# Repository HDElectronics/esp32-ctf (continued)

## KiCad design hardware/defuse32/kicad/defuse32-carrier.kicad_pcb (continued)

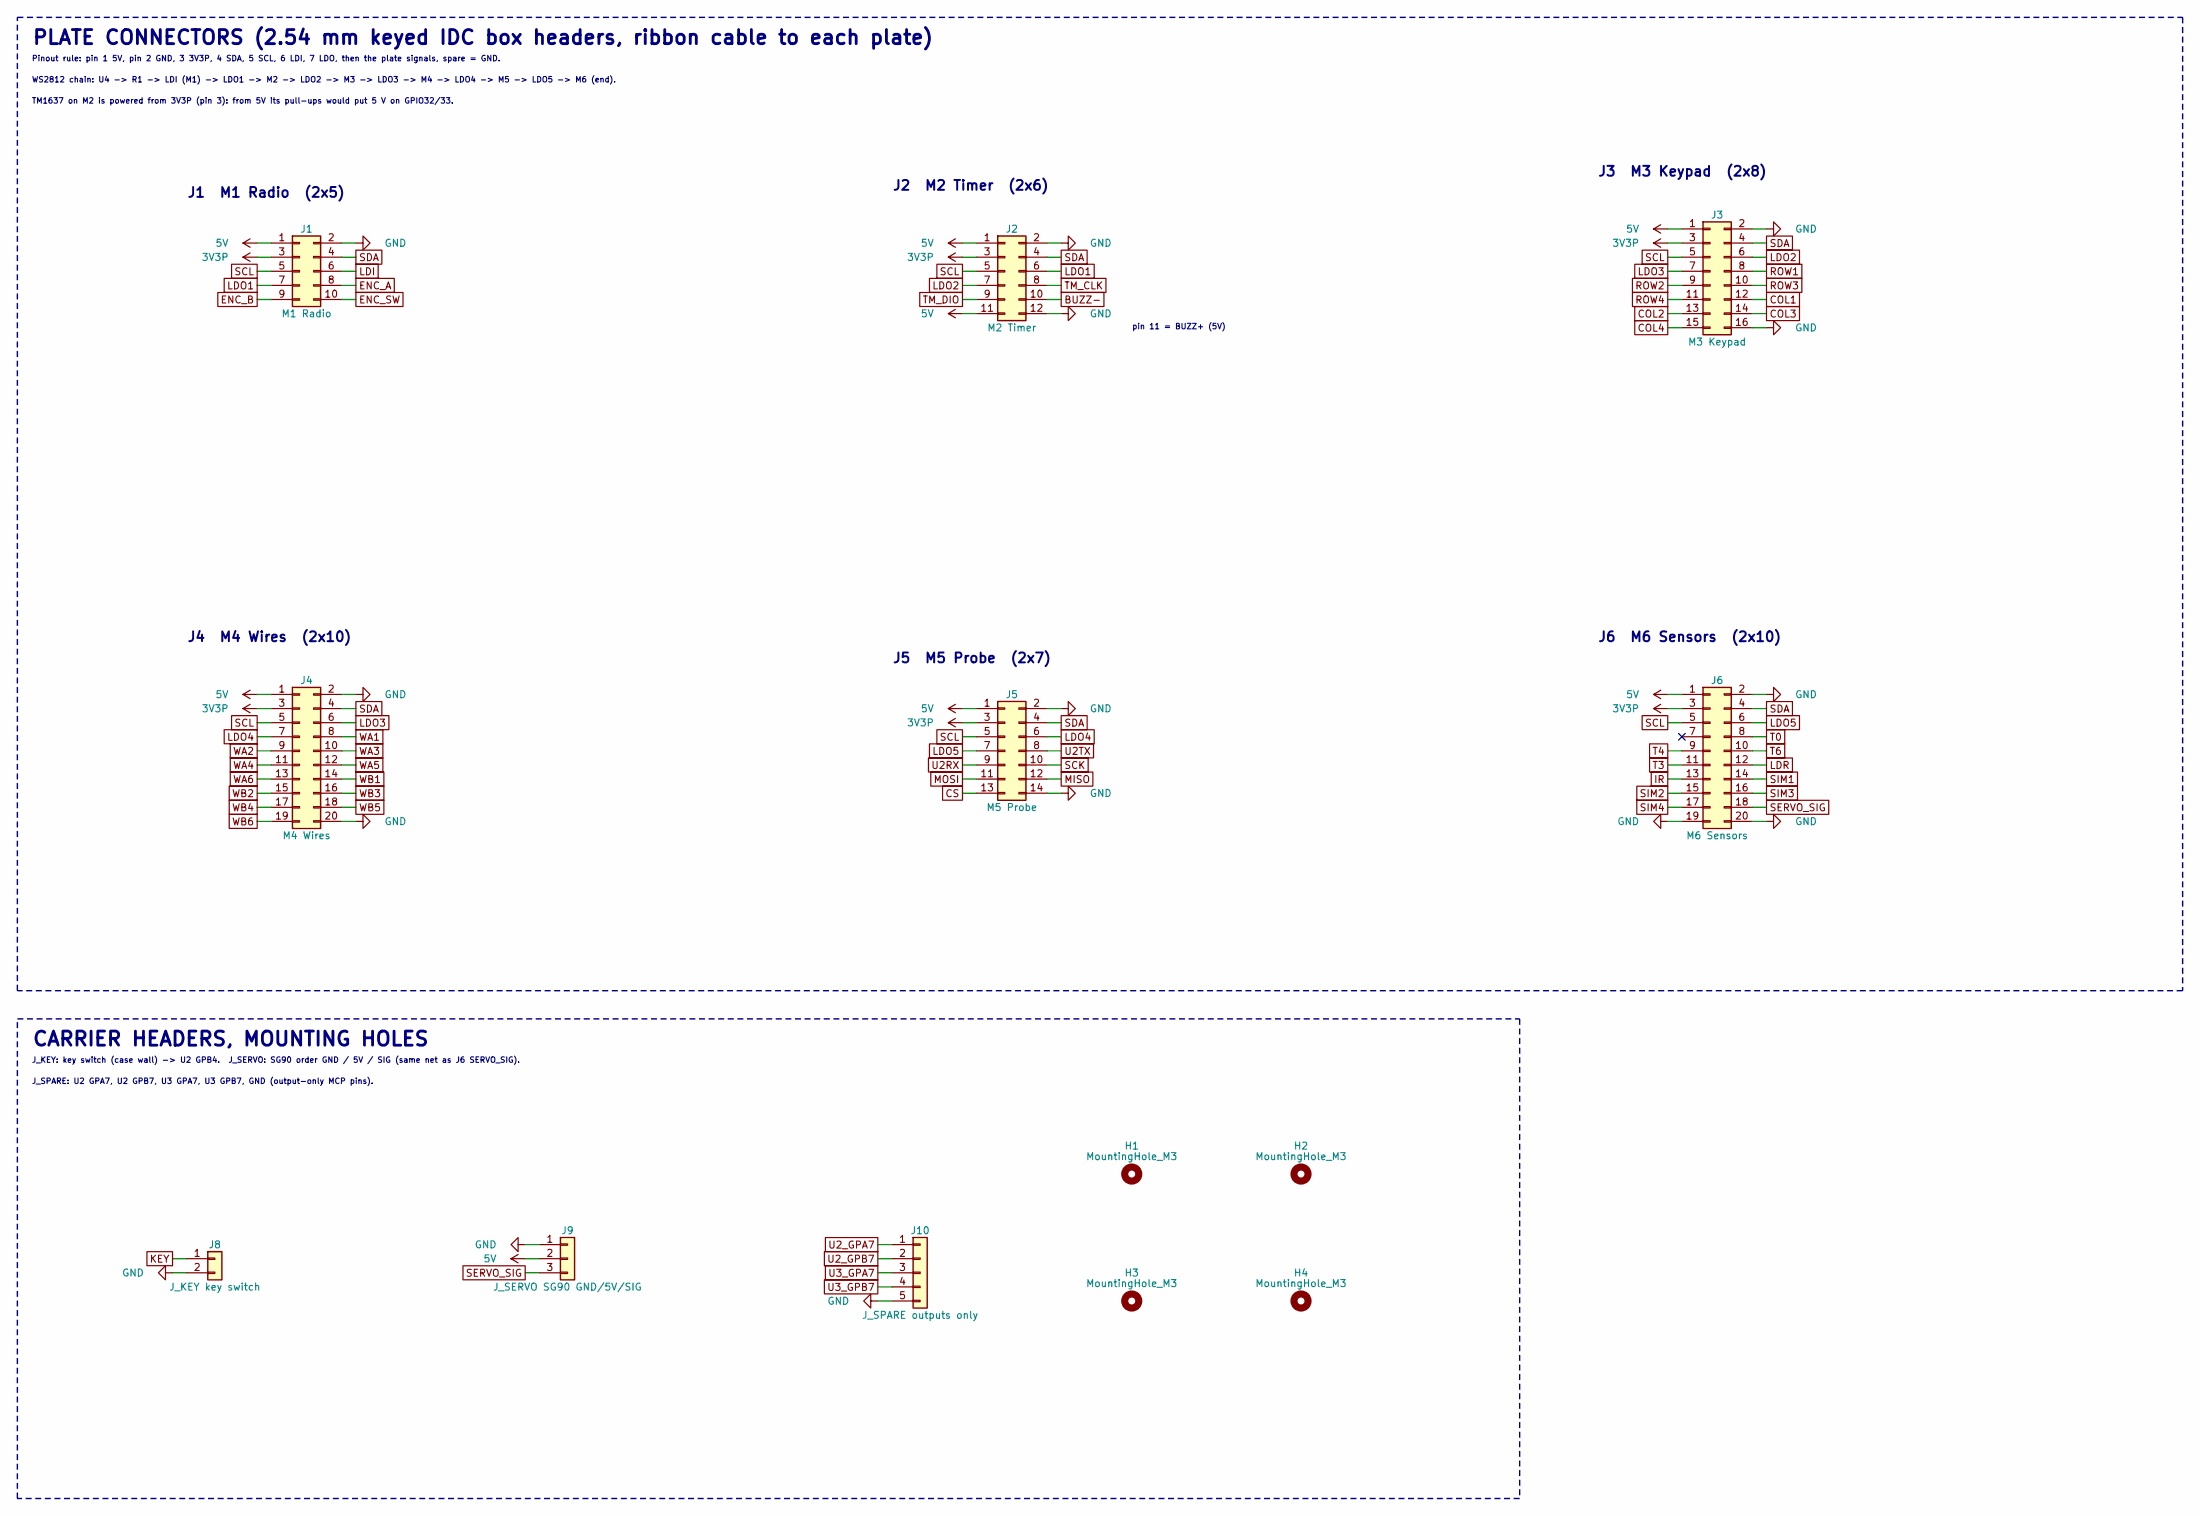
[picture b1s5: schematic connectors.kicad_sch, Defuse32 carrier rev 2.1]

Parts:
H1, H2, H3, H4: MountingHole_M3; MountingHole_3.2mm_M3
J1: M1 Radio; IDC-Header_2x05_P2.54mm_Vertical; MPN XDFH-0254-2*5P; LCSC C19193807
J2: M2 Timer; IDC-Header_2x06_P2.54mm_Vertical; MPN XDFH-0254-2*6P; LCSC C18202143
J3: M3 Keypad; IDC-Header_2x08_P2.54mm_Vertical; MPN XDFH-0254-2*8P; LCSC C18202144
J4: M4 Wires; IDC-Header_2x10_P2.54mm_Vertical; MPN XDFH-0254-2*10P; LCSC C18202145
J5: M5 Probe; IDC-Header_2x07_P2.54mm_Vertical; MPN XDFH-0254-2*7P; LCSC C19193808
J6: M6 Sensors; IDC-Header_2x10_P2.54mm_Vertical; MPN XDFH-0254-2*10P; LCSC C18202145
J8: J_KEY key switch; PinHeader_1x02_P2.54mm_Vertical; MPN HX PZ2.54-1x2P ZZ; LCSC C32713268
J9: J_SERVO SG90 GND/5V/SIG; PinHeader_1x03_P2.54mm_Vertical; MPN HX PZ2.54-1x3P ZZ; LCSC C32713269
J10: J_SPARE outputs only; PinHeader_1x05_P2.54mm_Vertical; MPN HX PZ2.54-1x5P ZZ; LCSC C32713271

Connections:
3V3P: J1.3, J2.3, J3.3, J4.3, J5.3, J6.3; also elsewhere on the board
5V: J1.1, J2.1, J2.11, J3.1, J4.1, J5.1, J6.1, J9.2; also elsewhere on the board
BUZZ-: J2.10; also elsewhere on the board
COL1: J3.12; also elsewhere on the board
COL2: J3.13; also elsewhere on the board
COL3: J3.14; also elsewhere on the board
COL4: J3.15; also elsewhere on the board
CS: J5.13; also elsewhere on the board
ENC_A: J1.8; also elsewhere on the board
ENC_B: J1.9; also elsewhere on the board
ENC_SW: J1.10; also elsewhere on the board
GND: J1.2, J2.2, J2.12, J3.2, J3.16, J4.2, J4.20, J5.2, J5.14, J6.2, J6.19, J6.20, J8.2, J9.1, J10.5; also elsewhere on the board
IR: J6.13; also elsewhere on the board
KEY: J8.1; also elsewhere on the board
LDI: J1.6; also elsewhere on the board
LDO1: J1.7, J2.6
LDO2: J2.7, J3.6
LDO3: J3.7, J4.6
LDO4: J4.7, J5.6
LDO5: J5.7, J6.6
LDR: J6.12; also elsewhere on the board
MISO: J5.12; also elsewhere on the board
MOSI: J5.11; also elsewhere on the board
ROW1: J3.8; also elsewhere on the board
ROW2: J3.9; also elsewhere on the board
ROW3: J3.10; also elsewhere on the board
ROW4: J3.11; also elsewhere on the board
SCK: J5.10; also elsewhere on the board
SCL: J1.5, J2.5, J3.5, J4.5, J5.5, J6.5; also elsewhere on the board
SDA: J1.4, J2.4, J3.4, J4.4, J5.4, J6.4; also elsewhere on the board
SERVO_SIG: J6.18, J9.3; also elsewhere on the board
SIM1: J6.14; also elsewhere on the board
SIM2: J6.15; also elsewhere on the board
SIM3: J6.16; also elsewhere on the board
SIM4: J6.17; also elsewhere on the board
T0: J6.8; also elsewhere on the board
T3: J6.11; also elsewhere on the board
T4: J6.9; also elsewhere on the board
T6: J6.10; also elsewhere on the board
TM_CLK: J2.8; also elsewhere on the board
TM_DIO: J2.9; also elsewhere on the board
U2RX: J5.9; also elsewhere on the board
U2TX: J5.8; also elsewhere on the board
U2_GPA7: J10.1; also elsewhere on the board
U2_GPB7: J10.2; also elsewhere on the board
U3_GPA7: J10.3; also elsewhere on the board
U3_GPB7: J10.4; also elsewhere on the board
WA1: J4.8; also elsewhere on the board
WA2: J4.9; also elsewhere on the board
WA3: J4.10; also elsewhere on the board
WA4: J4.11; also elsewhere on the board
WA5: J4.12; also elsewhere on the board
WA6: J4.13; also elsewhere on the board
WB1: J4.14; also elsewhere on the board
WB2: J4.15; also elsewhere on the board
WB3: J4.16; also elsewhere on the board
WB4: J4.17; also elsewhere on the board
WB5: J4.18; also elsewhere on the board
WB6: J4.19; also elsewhere on the board

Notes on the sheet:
PLATE CONNECTORS (2.54 mm keyed IDC box headers, ribbon cable to each plate)
Pinout rule: pin 1 5V, pin 2 GND, 3 3V3P, 4 SDA, 5 SCL, 6 LDI, 7 LDO, then the plate signals, spare = GND.
WS2812 chain: U4 -> R1 -> LDI (M1) -> LDO1 -> M2 -> LDO2 -> M3 -> LDO3 -> M4 -> LDO4 -> M5 -> LDO5 -> M6 (end).
TM1637 on M2 is powered from 3V3P (pin 3): from 5V its pull-ups would put 5 V on GPIO32/33.
CARRIER HEADERS, MOUNTING HOLES
J_KEY: key switch (case wall) -> U2 GPB4. J_SERVO: SG90 order GND / 5V / SIG (same net as J6 SERVO_SIG).
J_SPARE: U2 GPA7, U2 GPB7, U3 GPA7, U3 GPB7, GND (output-only MCP pins).
J1 M1 Radio (2x5)
J2 M2 Timer (2x6)
J3 M3 Keypad (2x8)
J4 M4 Wires (2x10)
J5 M5 Probe (2x7)
J6 M6 Sensors (2x10)
pin 11 = BUZZ+ (5V)

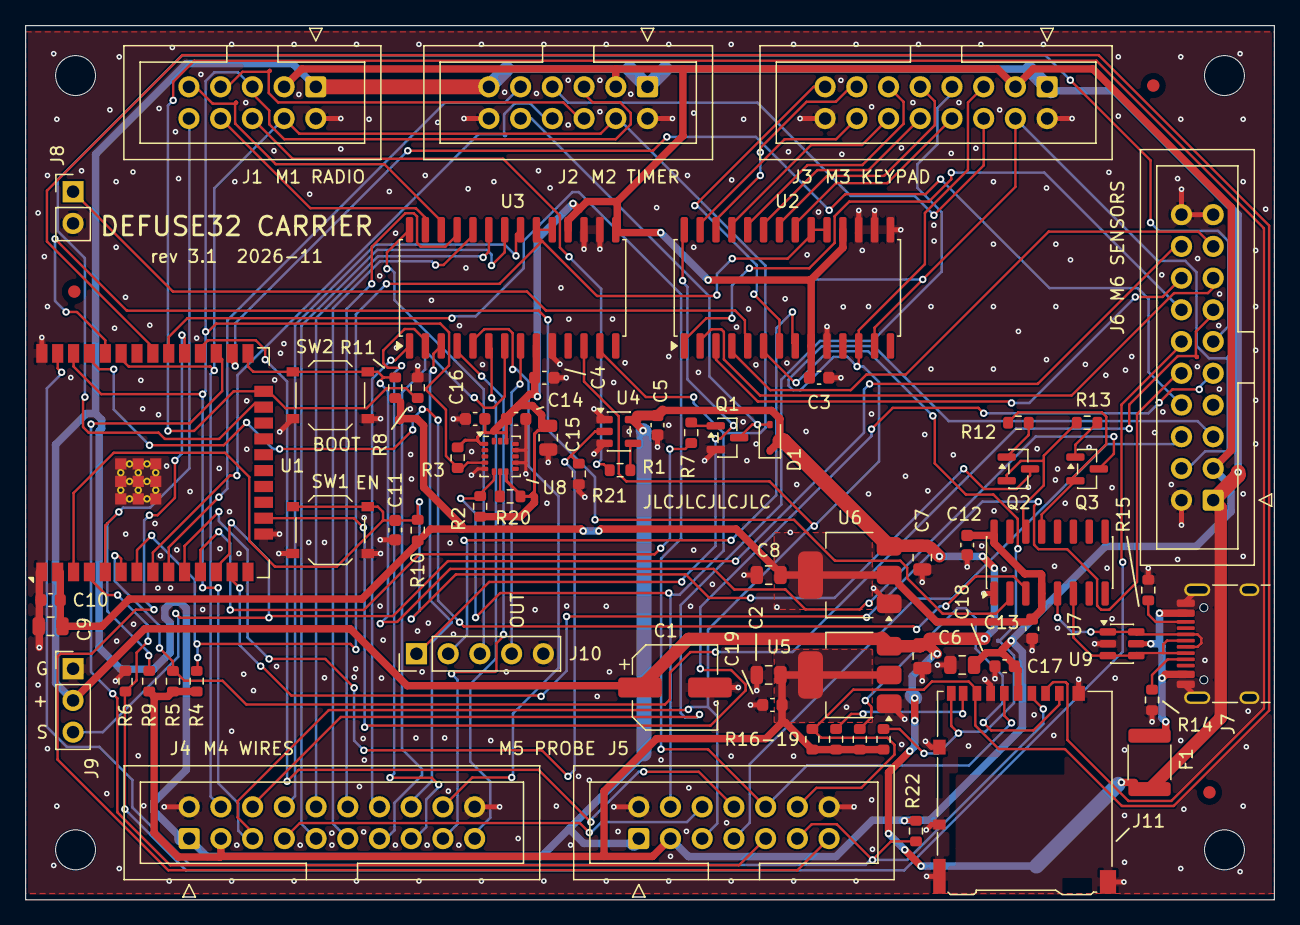
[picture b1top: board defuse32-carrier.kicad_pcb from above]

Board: 4 copper layers, 100.0 x 70.0 mm, 75 parts (0 on the bottom side), 83 nets.

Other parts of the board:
FID1, FID2, FID3: Fiducial; Fiducial_1mm_Mask2mm

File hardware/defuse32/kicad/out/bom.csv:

"Refs","Value","Footprint","Qty","LCSC","MPN","Manufacturer","JLC"
"C1","220uF/10V","Capacitor_SMD:CP_Elec_6.3x5.4","1","C72494","RVT1A221M0605","ROQANG","Extended"
"C2,C8","22uF","Capacitor_SMD:C_0805_2012Metric","2","C45783","CL21A226MAQNNNE","Samsung","Basic"
"C3-C5,C10,C12-C14,C16,C17,C19","100nF","Capacitor_SMD:C_0603_1608Metric","10","C14663","CC0603KRX7R9BB104","YAGEO","Basic"
"C6,C7,C9,C15,C18","10uF","Capacitor_SMD:C_0805_2012Metric","5","C15850","CL21A106KAYNNNE","Samsung","Basic"
"C11","1uF","Capacitor_SMD:C_0603_1608Metric","1","C15849","CL10A105KB8NNNC","Samsung","Basic"
"D1","1N4148WS","Diode_SMD:D_SOD-323","1","C2128","1N4148WS","Changjiang (CJ)","Basic"
"F1","PTC 2A","Fuse:Fuse_1812_4532Metric","1","C18198338","1812L200/8GR","LUTE","Extended"
"J1","M1 Radio","Connector_IDC:IDC-Header_2x05_P2.54mm_Vertical","1","C19193807","XDFH-0254-2*5P","Lian Xin","Extended"
"J2","M2 Timer","Connector_IDC:IDC-Header_2x06_P2.54mm_Vertical","1","C18202143","XDFH-0254-2*6P","Lian Xin","Extended"
"J3","M3 Keypad","Connector_IDC:IDC-Header_2x08_P2.54mm_Vertical","1","C18202144","XDFH-0254-2*8P","Lian Xin","Extended"
"J4","M4 Wires","Connector_IDC:IDC-Header_2x10_P2.54mm_Vertical","1","C18202145","XDFH-0254-2*10P","Lian Xin","Extended"
"J5","M5 Probe","Connector_IDC:IDC-Header_2x07_P2.54mm_Vertical","1","C19193808","XDFH-0254-2*7P","Lian Xin","Extended"
"J6","M6 Sensors","Connector_IDC:IDC-Header_2x10_P2.54mm_Vertical","1","C18202145","XDFH-0254-2*10P","Lian Xin","Extended"
"J7","J_USB USB-C","defuse32:USB_C_Receptacle_HRO_TYPE-C-31-M-12_Edge","1","C165948","TYPE-C-31-M-12","Korean Hroparts Elec","Extended"
"J8","J_KEY key switch","Connector_PinHeader_2.54mm:PinHeader_1x02_P2.54mm_Vertical","1","C32713268","HX PZ2.54-1x2P ZZ","hanxia","Extended"
"J9","J_SERVO SG90 GND/5V/SIG","Connector_PinHeader_2.54mm:PinHeader_1x03_P2.54mm_Vertical","1","C32713269","HX PZ2.54-1x3P ZZ","hanxia","Extended"
"J10","J_SPARE outputs only","Connector_PinHeader_2.54mm:PinHeader_1x05_P2.54mm_Vertical","1","C32713271","HX PZ2.54-1x5P ZZ","hanxia","Extended"
"J11","J_SD microSD push-push","Connector_Card:microSD_HC_Hirose_DM3AT-SF-PEJM5","1","C114218","DM3AT-SF-PEJM5","Hirose","Extended"
"Q1","SS8050","Package_TO_SOT_SMD:SOT-23","1","C2150","SS8050(RANGE:200-350)","JSCJ (Changjiang)","Basic"
"Q2,Q3","MMBT3904","Package_TO_SOT_SMD:SOT-23","2","C20526","MMBT3904","Changjiang (CJ)","Basic"
"R1,R7","330","Resistor_SMD:R_0603_1608Metric","2","C23138","0603WAF3300T5E","UNI-ROYAL","Basic"
"R2,R3","4.7k","Resistor_SMD:R_0603_1608Metric","2","C23162","0603WAF4701T5E","UNI-ROYAL","Basic"
"R4-R6,R8-R13,R16-R22","10k","Resistor_SMD:R_0603_1608Metric","16","C25804","0603WAF1002T5E","UNI-ROYAL","Basic"
"R14,R15","5.1k","Resistor_SMD:R_0603_1608Metric","2","C23186","0603WAF5101T5E","UNI-ROYAL","Basic"
"SW1","EN","Button_Switch_SMD:SW_Push_1P1T_XKB_TS-1187A","1","C318884","TS-1187A-B-A-B","XKB Connection","Basic"
"SW2","BOOT","Button_Switch_SMD:SW_Push_1P1T_XKB_TS-1187A","1","C318884","TS-1187A-B-A-B","XKB Connection","Basic"
"U1","ESP32-WROOM-32E-N4","defuse32:ESP32-WROOM-32E_JLC","1","C701341","ESP32-WROOM-32E-N4","Espressif","Extended"
"U2","MCP23017-E/SO (0x20)","Package_SO:SOIC-28W_7.5x17.9mm_P1.27mm","1","C47023","MCP23017-E/SO","Microchip","Extended"
"U3","MCP23017-E/SO (0x21)","Package_SO:SOIC-28W_7.5x17.9mm_P1.27mm","1","C47023","MCP23017-E/SO","Microchip","Extended"
"U4","74AHCT1G125","Package_TO_SOT_SMD:SOT-23-5","1","C7484","SN74AHCT1G125DBVR","Texas Instruments","Extended"
"U5,U6","AMS1117-3.3","Package_TO_SOT_SMD:SOT-223-3_TabPin2","2","C6186","AMS1117-3.3","Advanced Monolithic Systems","Basic"
"U7","CH340C","Package_SO:SOIC-16_3.9x9.9mm_P1.27mm","1","C84681","CH340C","WCH","Extended"
"U8","LIS3DH (0x19)","Package_LGA:LGA-16_3x3mm_P0.5mm_LayoutBorder3x5y","1","C15134","LIS3DHTR","STMicroelectronics","Extended"
"U9","USBLC6-2SC6","Package_TO_SOT_SMD:SOT-23-6","1","C7519","USBLC6-2SC6","STMicroelectronics","Extended"

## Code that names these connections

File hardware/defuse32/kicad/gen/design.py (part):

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# ESP32 pin map (SPEC "ESP32 pin map", unchanged): module pin -> net
GND_STACK = "[1,15,38,39]"   # stacked GND pin of RF_Module:ESP32-WROOM-32E (pads 1, 15, 38, 39)
U1 = {GND_STACK: "GND", "2": "3V3", "3": "EN",
      "4": "LDR",        # SENSOR_VP GPIO36
      "5": "ENC_SW",     # SENSOR_VN GPIO39 (rev 1b)
      "6": "IR",         # GPIO34
      "7": "MCP_INT",    # GPIO35
      "8": "TM_CLK",     # GPIO32
      "9": "TM_DIO",     # GPIO33
      "10": "WS_DATA",   # GPIO25
      "11": "BUZZ",      # GPIO26
      "12": "SERVO_SIG",  # GPIO27
      "13": "T6",        # GPIO14
      "14": NC,          # GPIO12 strapping, unused
      "16": "T4",        # GPIO13
      "23": "T3",        # GPIO15
      "24": "SD_CS",     # GPIO2
      "25": "IO0",       # GPIO0 boot
      "26": "T0",        # GPIO4
      "27": "U2RX",      # GPIO16
      "28": "U2TX",      # GPIO17
      "29": "CS",        # GPIO5
      "30": "SCK",       # GPIO18
      "31": "MISO",      # GPIO19
      "33": "SDA",       # GPIO21
      "34": "U0RXD",     # RXD0 GPIO3
      "35": "U0TXD",     # TXD0 GPIO1
      "36": "SCL",       # GPIO22
      "37": "MOSI",      # GPIO23
      }
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# pull-ups / pull-downs (SPEC "Electronics" R row; rev 1b R9)
R("R2", "4.7k", "3V3P", "SDA", "mcu", (243.84, 48.26), note="I2C SDA pull-up")
R("R3", "4.7k", "3V3P", "SCL", "mcu", (254.0, 48.26), note="I2C SCL pull-up")
R("R4", "10k", "3V3P", "MCP_INT", "mcu", (269.24, 48.26), note="GPIO35 pull-up")
R("R5", "10k", "3V3P", "IR", "mcu", (279.4, 48.26), note="GPIO34 pull-up")
R("R9", "10k", "3V3P", "ENC_SW", "mcu", (289.56, 48.26), note="GPIO39 pull-up")
R("R6", "10k", "LDR", "GND", "mcu", (309.88, 48.26), note="LDR divider low side")
R("R8", "10k", "SD_CS", "GND", "mcu", (325.12, 48.26), note="GPIO2 pull-down")

# WS2812 buffer 3V3 -> 5V: 74AHCT1G125, OE low (pin 1 OE#, 2 A, 3 GND, 4 Y, 5 VCC)
part("U4", "74xGxx", "74AHCT1G125", "74AHCT1G125", "Package_TO_SOT_SMD:SOT-23-5",
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     lcsc="AHCT1G125")
R("R1", "330", "WS_5V", "LDI", "mcu", (330.2, 134.62), rot=90, note="WS2812 data series R")
C("C5", "100nF", "5V", "GND", "mcu", (358.14, 134.62), note="U4")
# rev 2.1 (review D19): WS_DATA (GPIO25) is high-Z during reset and U4's OE is tied low: a pull-down keeps
# the buffer input defined (no random first-LED data at power-up)
R("R21", "10k", "WS_DATA", "GND", "mcu", (243.84, 134.62), note="WS_DATA pull-down")

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    5: ("Probe", 7, ["U2TX", "U2RX", "SCK", "MOSI", "MISO", "CS"]),
    6: ("Sensors", 10, ["T0", "T4", "T6", "T3", "LDR", "IR", "SIM1", "SIM2", "SIM3", "SIM4", "SERVO_SIG"]),
}
PLATE_PINNAMES = {2: {11: "BUZZ+ (5V)"}}
# WS2812 chain: U4 -> R1 -> LDI (M1) -> LDO1 (M1 out = M2 in) ... -> M6 LDO (chain end, NC)
LD_IN = {1: "LDI", 2: "LDO1", 3: "LDO2", 4: "LDO3", 5: "LDO4", 6: "LDO5"}
LD_OUT = {1: "LDO1", 2: "LDO2", 3: "LDO3", 4: "LDO4", 5: "LDO5", 6: NC}
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        (295.91, 15.24, 405.13, 63.5, "POWER FLAGS (ERC)", []),
        (15.24, 139.7, 290.83, 281.94, "USB-UART (CH340C) AND AUTO-RESET", [
            ("CH340C at 3.3 V: V3 tied to VCC (local symbol CH340C_3V3: pin 4 typed power_in). No crystal.", 17.78, 147.32),
            ("UART0: CH340C TXD -> U0RXD (GPIO3), RXD <- U0TXD (GPIO1). CTS/DSR/RI/DCD, R232 unused.", 17.78, 151.13),
            ("Auto-reset, esptool levels (CH340C pins inverted): DTR=0 RTS=1 -> Q2 pulls EN low; DTR=1 RTS=0 -> Q3 pulls IO0 low; equal: released.", 129.54, 251.46),
            ("EN RC (R10 10k + C11 1 uF) and the IO0 pull-up R11 are on the ESP32 sheet.", 129.54, 255.27),
        ]),
    ],
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        (15.24, 15.24, 226.06, 200.66, "ESP32-WROOM-32E (U1)", [
            ("Soldered at the left board edge, antenna end outward: the antenna region is outside the outline,", 17.78, 160.02),
            ("no copper under or around it (keep-out in the footprint).", 17.78, 163.83),
            ("GPIO2 = SD_CS (R8 pull-down keeps the strapping valid). GPIO12: strapping, unused (NC).", 17.78, 167.64),
            ("GPIO0/1/3: boot and UART0 console (CH340C). GPIO6-11: module flash (NC pins).", 17.78, 171.45),
            ("EN: R10 10k + C11 1 uF, SW1. BOOT: SW2 on IO0 with R11 10k pull-up.", 17.78, 175.26),
        ]),
        (231.14, 15.24, 405.13, 95.25, "PULL-UPS, PULL-DOWNS", [
            ("R2/R3 I2C 4.7k; R4 GPIO35 (MCP_INT), R5 GPIO34 (IR), R9 GPIO39 (ENC_SW) 10k to 3V3P.", 233.68, 81.28),
            ("R6: LDR divider low side (LDR on M6 from 3V3P -> GPIO36). R8: GPIO2 (SD_CS) pull-down.", 233.68, 85.09),
        ]),
        (231.14, 100.33, 405.13, 165.1, "WS2812 BUFFER 3V3 -> 5V", [
            ("U4 74AHCT1G125 at 5 V, OE low. R1 330R in series, R21 10k pull-down on WS_DATA. Chain: LDI -> M1 ... M6.", 233.68, 158.75),
        ]),
        (231.14, 170.18, 405.13, 245.11, "BUZZER DRIVER", [
            ("GPIO26 (BUZZ, LEDC PWM) -> R7 330R -> Q1 SS8050. Buzzer on M2: BUZZ+ = 5V (J2 pin 11), BUZZ- on J2 pin 10.", 233.68, 237.49),
        ]),
    ],
    "io": [
        (15.24, 15.24, 250.19, 147.32, "I2C EXPANDERS (U2 0x20, U3 0x21)", [
            ("INTA/INTB of both chips: mirrored, open-drain, wired-OR to GPIO35 (MCP_INT).", 17.78, 137.16),
            ("U2: keypad ROW1-4 GPA0-3, COL1-3 GPA4-6, COL4 GPB6, Simon SIM1-4 GPB0-3, KEY GPB4, SD_DET GPB5.", 17.78, 140.97),
            ("U3: wire posts WA1-5 GPA0-4, WA6 GPB6, WB1-6 GPB0-5, ENC_A/B GPA6/5. GPA7/GPB7: output-only -> J_SPARE.", 17.78, 144.78),
        ]),
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            ("Replaces the rev 1 GY-521 / MPU-6050.", 257.81, 110.49),
        ]),
        (255.27, 121.92, 405.13, 245.11, "microSD (push-push, SPI mode)", [
            ("VSPI shared with the probe plate: SCK GPIO18, MOSI GPIO23, MISO GPIO19, SD_CS GPIO2.", 257.81, 229.87),
            ("DAT0-2 and CMD (R22) 10k pull-ups to 3V3P. Card detect: DET_A GND, DET_B -> SD_DET (U2 GPB5), R19:", 257.81, 233.68),
            ("low = card present: the DM3 detect switch is normally open and closes on insertion (Hirose DM3", 257.81, 237.49),
            ("catalog). Firmware: CONFIG_D32_SD_DET_ACTIVE_HIGH=n.", 257.81, 241.3),
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    ],
    "conn": [
        (15.24, 15.24, 405.13, 190.5, "PLATE CONNECTORS (2.54 mm keyed IDC box headers, ribbon cable to each plate)", [
            ("Pinout rule: pin 1 5V, pin 2 GND, 3 3V3P, 4 SDA, 5 SCL, 6 LDI, 7 LDO, then the plate signals, spare = GND.", 17.78, 22.86),
            ("WS2812 chain: U4 -> R1 -> LDI (M1) -> LDO1 -> M2 -> LDO2 -> M3 -> LDO3 -> M4 -> LDO4 -> M5 -> LDO5 -> M6 (end).", 17.78, 26.67),
            ("TM1637 on M2 is powered from 3V3P (pin 3): from 5V its pull-ups would put 5 V on GPIO32/33.", 17.78, 30.48),
        ]),
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    "R16": (63.0, 57.15, 90), "R17": (64.9, 57.15, 90), "R18": (66.8, 57.15, 90), "R19": (68.7, 57.15, 90),
    # rev 2.1 additions, placed on the routed board by gen/std_fixes.py (new_parts) in free spots found by
    # search (courtyard clear, pads clear of other-net copper, nearest copper of both nets)
    "R21": (44.3, 35.9, 270),             # WS_DATA pull-down, below the GPIO25 -> U4 pin 2 track, left of U4
    "R22": (71.3, 64.5, 270),             # SD CMD (MOSI) pull-up, left of J11 on the MOSI / 3V3P tracks
}
# J7 stands USBC_OUT past the right edge (2026-11-26): flush with the edge, the body of a seated plug ends only
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
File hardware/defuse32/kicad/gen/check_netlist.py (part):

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

# SPEC "ESP32 pin map" (fixed): GPIO -> net. None = unused/NC.
SPEC_GPIO = {21: "SDA", 22: "SCL", 35: "MCP_INT", 39: "ENC_SW", 34: "IR", 36: "LDR", 32: "TM_CLK",
             33: "TM_DIO", 25: "WS_DATA", 26: "BUZZ", 27: "SERVO_SIG", 4: "T0", 13: "T4", 14: "T6", 15: "T3",
             18: "SCK", 23: "MOSI", 19: "MISO", 5: "CS", 17: "U2TX", 16: "U2RX", 2: "SD_CS", 12: None,
             0: "IO0", 1: "U0TXD", 3: "U0RXD"}     # 0/1/3: boot + UART0 to the CH340C (rev 2)
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        expect(got, "J7", pin, "VBUS", "USB-C VBUS")
    for pin in ("A1", "A12", "B1", "B12", "SH"):
        expect(got, "J7", pin, "GND", "USB-C GND")
    for pin, net in (("A5", "CC1"), ("B5", "CC2"), ("A6", "USB_DP"), ("B6", "USB_DP"), ("A7", "USB_DM"),
                     ("B7", "USB_DM")):
        expect(got, "J7", pin, net, "USB-C")
    for r, cc in (("R14", "CC1"), ("R15", "CC2")):
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        expect(got, r, "2", "GND", "CC 5.1k")
    expect(got, "F1", "1", "VBUS", "PTC")
    expect(got, "F1", "2", "5V", "PTC")
    for pin, net in (("1", "USB_DP"), ("6", "USB_DP"), ("3", "USB_DM"), ("4", "USB_DM"), ("5", "VBUS"), ("2", "GND")):
        expect(got, "U9", pin, net, "USBLC6")
    for pin, net in (("5", "USB_DP"), ("6", "USB_DM"), ("2", "U0RXD"), ("3", "U0TXD"), ("13", "DTR"), ("14", "RTS"),
                     ("16", "3V3"), ("4", "3V3"), ("1", "GND")):
        expect(got, "U7", pin, net, "CH340C")
    for q, b, e, c in (("Q2", "AR_DTR_B", "RTS", "EN"), ("Q3", "AR_RTS_B", "DTR", "IO0")):
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    expect(got, "R13", "1", "RTS", "auto-reset")

    # 7. LIS3DH (0x19, I2C), microSD
    for pin, net in (("4", "SCL"), ("6", "SDA"), ("7", "LIS_SA0"), ("8", "3V3P"), ("9", None), ("11", None)):
        expect(got, "U8", pin, net, "LIS3DH")
    expect(got, "R20", "1", "3V3P", "LIS3DH SA0 high")
    expect(got, "R20", "2", "LIS_SA0", "LIS3DH SA0 high")
    for pin, net in (("2", "SD_CS"), ("3", "MOSI"), ("5", "SCK"), ("7", "MISO"), ("9", "SD_DET"), ("10", "GND")):
        expect(got, "J11", pin, net, "microSD")
    for r, net in (("R16", "MISO"), ("R17", "SD_DAT1"), ("R18", "SD_DAT2"), ("R19", "SD_DET")):
        expect(got, r, "1", "3V3P", "microSD pull-up")
        expect(got, r, "2", net, "microSD pull-up")
    expect(got, "R8", "1", "SD_CS", "GPIO2 pull-down")
    expect(got, "R8", "2", "GND", "GPIO2 pull-down")

    # 8. schematic rev 2.1 (2026-11-25, owner-approved): buzzer driver, WS_DATA pull-down, SD CMD pull-up
    for pin, net in (("1", "BUZZ_B"), ("2", "GND"), ("3", "BUZZ-")):
        expect(got, "Q1", pin, net, "buzzer driver (SS8050 SOT-23: 1 B, 2 E, 3 C)")
    expect(got, "R7", "1", "BUZZ", "buzzer base resistor")
    expect(got, "R7", "2", "BUZZ_B", "buzzer base resistor")
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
